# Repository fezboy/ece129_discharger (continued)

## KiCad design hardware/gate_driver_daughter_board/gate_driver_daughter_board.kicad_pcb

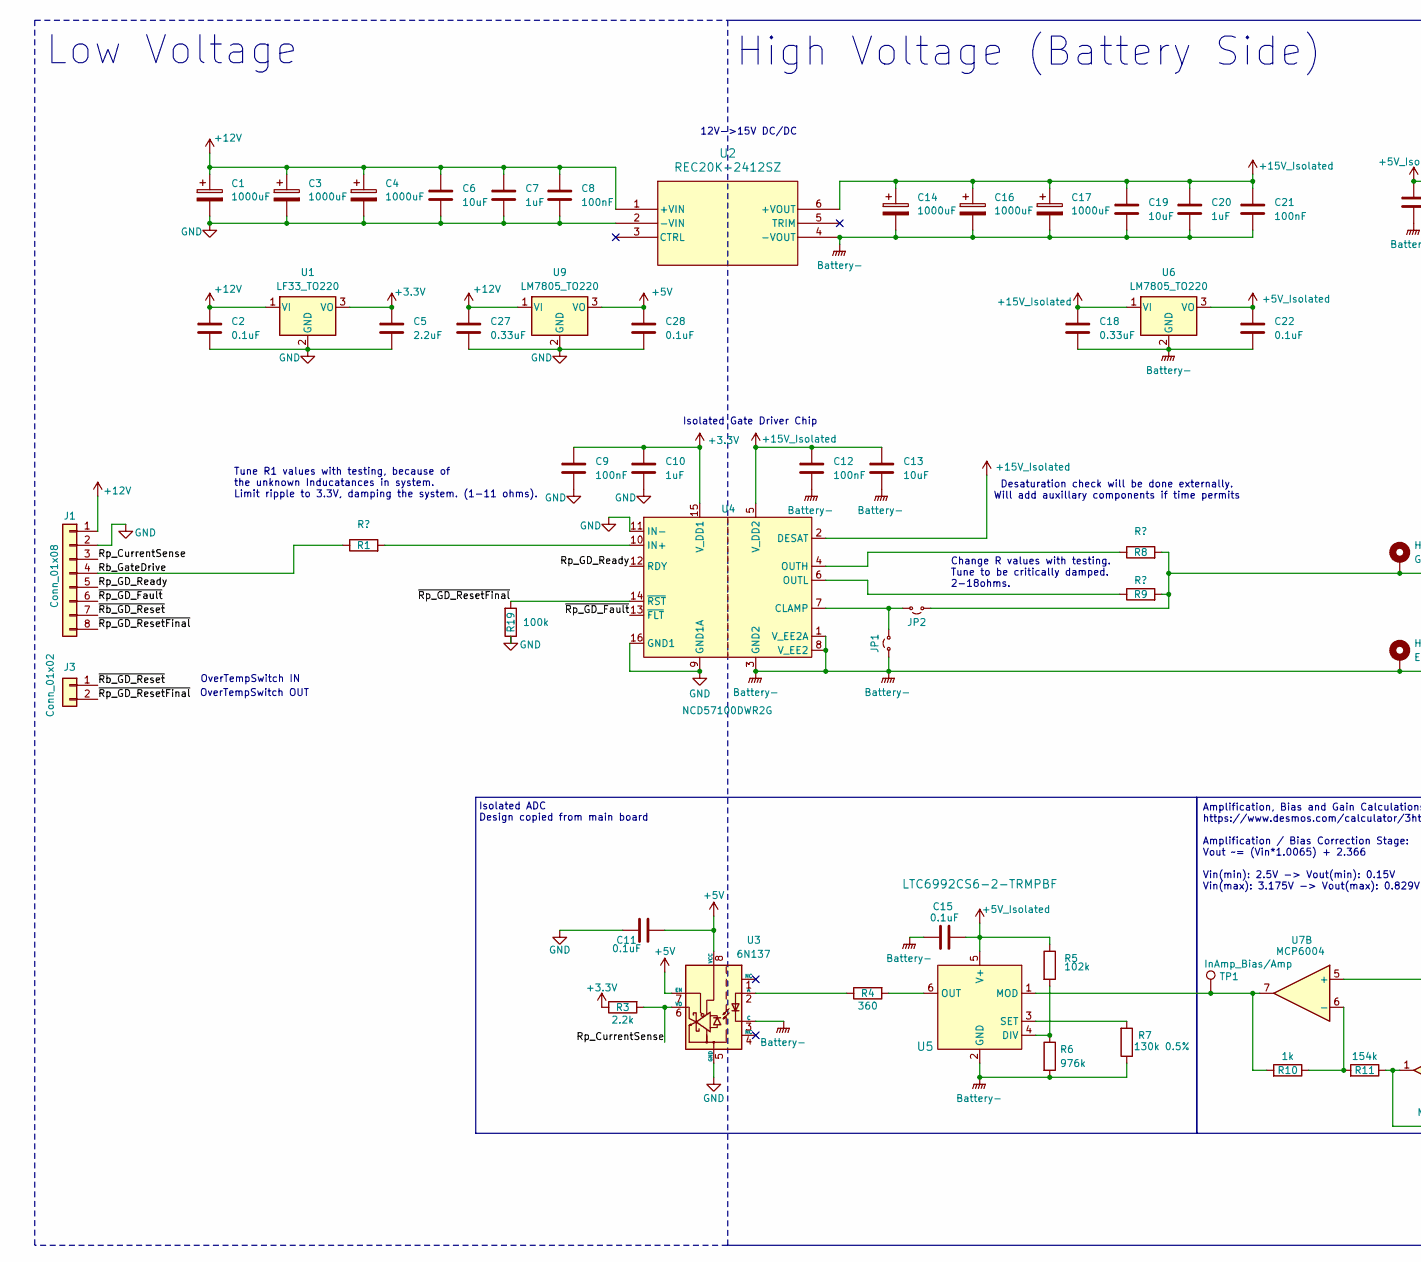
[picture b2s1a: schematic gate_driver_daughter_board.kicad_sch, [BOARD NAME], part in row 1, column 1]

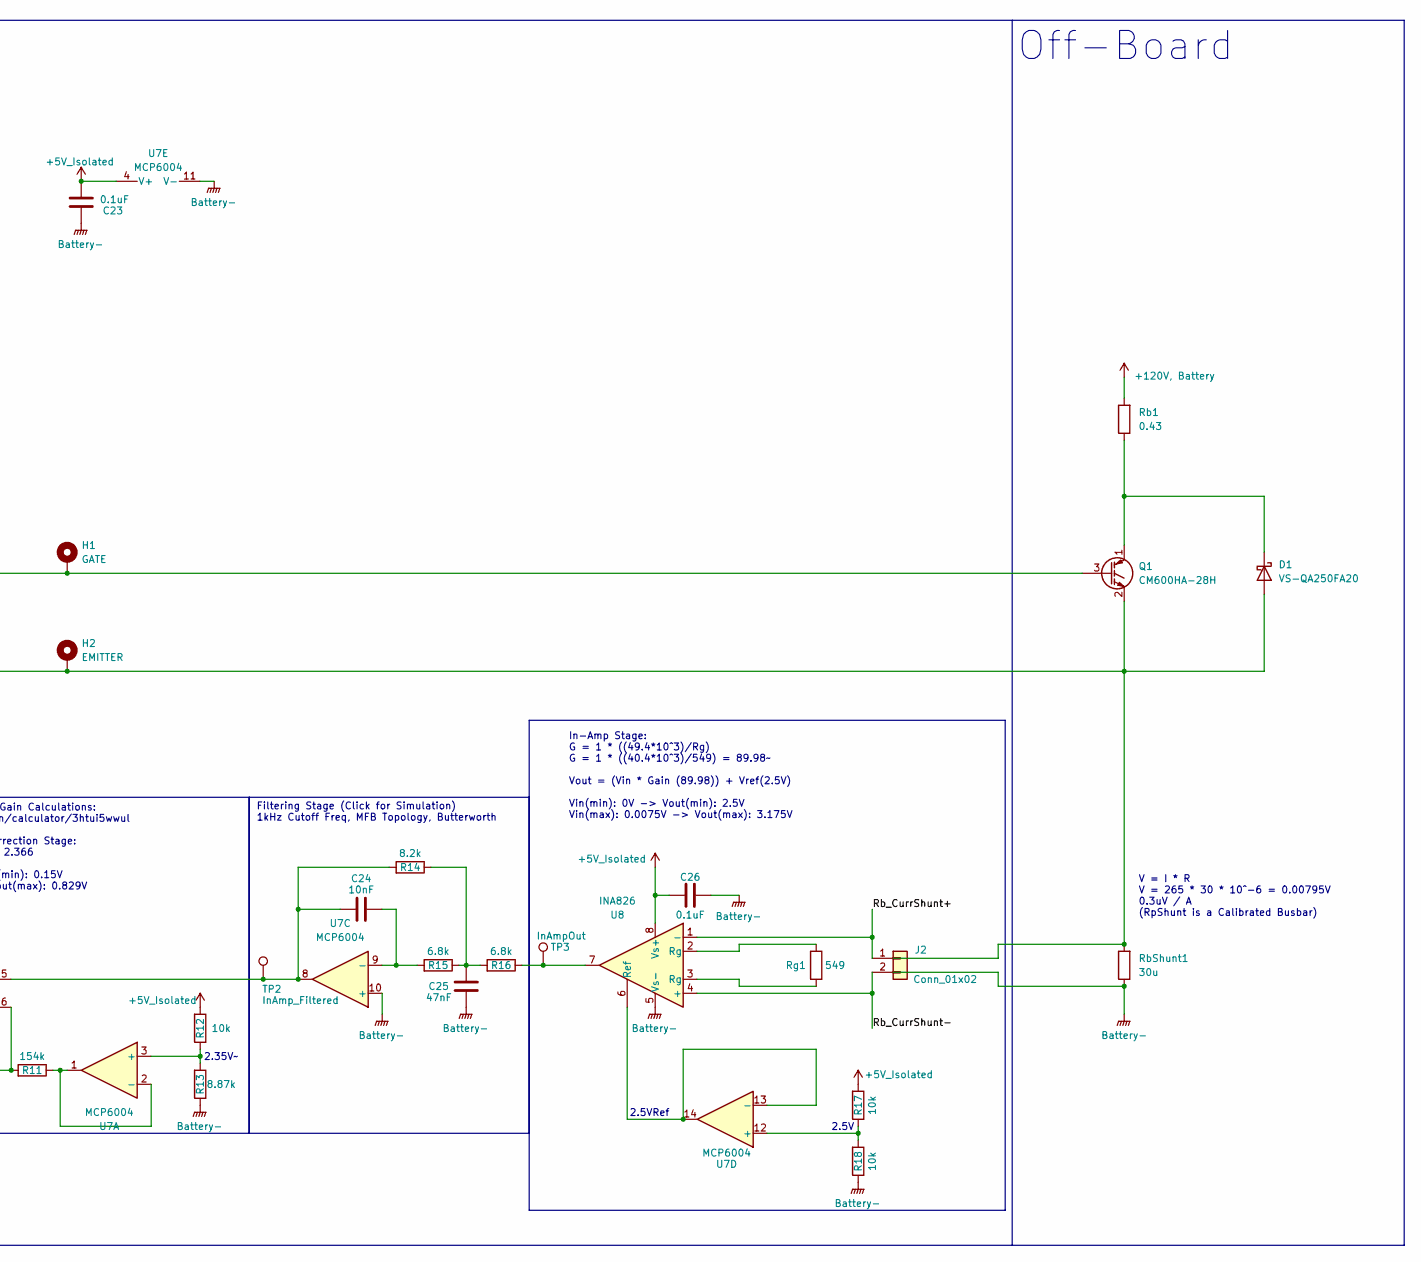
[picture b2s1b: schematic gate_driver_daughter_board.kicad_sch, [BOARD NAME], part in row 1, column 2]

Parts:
C1, C3, C4, C14, C16, C17: 1000uF; 25V1000uF; Manufacturer Part Number Nichicon; Digikey Part Number UVY1E102MPD1TD
C2, C11, C15, C22, C23, C26, C28: 0.1uF; C_0805_2012Metric_Pad1.18x1.45mm_HandSolder
C5: 2.2uF; C_0805_2012Metric_Pad1.18x1.45mm_HandSolder
C6, C13, C19: 10uF; C_0805_2012Metric_Pad1.18x1.45mm_HandSolder
C7, C10, C20: 1uF; C_0805_2012Metric_Pad1.18x1.45mm_HandSolder
C8, C9, C12, C21: 100nF; C_0805_2012Metric_Pad1.18x1.45mm_HandSolder
C18, C27: 0.33uF; C_0805_2012Metric_Pad1.18x1.45mm_HandSolder
C24: 10nF; C_0805_2012Metric_Pad1.18x1.45mm_HandSolder
C25: 47nF; C_0805_2012Metric_Pad1.18x1.45mm_HandSolder
D1: VS-QA250FA20; Manufacturer Part Number Vishay Semiconductors; Digikey Part Number 78-VS-QA250FA20
H1: GATE; MountingHole_4.3x6.2mm_M4_Pad
H2: EMITTER; MountingHole_4.3x6.2mm_M4_Pad
J1: Conn_01x08; Molex_Nano-Fit_105309-xx08_1x08_P2.50mm_Vertical
J2, J3: Conn_01x02; Molex_Nano-Fit_105309-xx02_1x02_P2.50mm_Vertical
JP1, JP2: Jumper_2_Small_Open; PinHeader_1x02_P2.54mm_Vertical
Q1: CM600HA-28H
R1, R8, R9: R?; R_1206_3216Metric_Pad1.30x1.75mm_HandSolder
R3: 2.2k; R_0805_2012Metric_Pad1.20x1.40mm_HandSolder
R4: 360; R_0805_2012Metric_Pad1.20x1.40mm_HandSolder
R5: 102k; R_0805_2012Metric_Pad1.20x1.40mm_HandSolder
R6: 976k; R_0805_2012Metric_Pad1.20x1.40mm_HandSolder
R7: 130k 0.5%; R_0805_2012Metric_Pad1.20x1.40mm_HandSolder
R10: 1k; R_0805_2012Metric_Pad1.20x1.40mm_HandSolder
R11: 154k; R_0805_2012Metric_Pad1.20x1.40mm_HandSolder
R12, R17, R18: 10k; R_0805_2012Metric_Pad1.20x1.40mm_HandSolder
R13: 8.87k; R_0805_2012Metric_Pad1.20x1.40mm_HandSolder
R14: 8.2k; R_0805_2012Metric_Pad1.20x1.40mm_HandSolder
R15, R16: 6.8k; R_0805_2012Metric_Pad1.20x1.40mm_HandSolder
R19: 100k; R_0805_2012Metric_Pad1.20x1.40mm_HandSolder
Rb1: 0.43
RbShunt1: 30u
Rg1: 549; R_0805_2012Metric_Pad1.20x1.40mm_HandSolder
TP1: InAmp_Bias/Amp; TestPoint_Pad_D3.0mm
TP2: InAmp_Filtered; TestPoint_Pad_D3.0mm
TP3: InAmpOut; TestPoint_Pad_2.0x2.0mm
U1: LF33_TO220; TO-220-3_Vertical
U2: REC20K-2412SZ; REC20K_RCP
U3: 6N137; DIP-8_W7.62mm
U4: NCD57100DWR2G; SOIC-16W_7.5x10.3mm_P1.27mm; MFG PN NCD57100DWR2G; Digi PN 488-NCD57100DWR2GTR-ND
U5: LTC6992CS6-2-TRMPBF; TSOT-23-6; MFG PN LTC6992CS6-2-TRMPBF; Digi PN 505-LTC6992CS6-2#TRMPBFCT-ND
U6, U9: LM7805_TO220; TO-220-3_Vertical
U7: MCP6004; SOIC-14_3.9x8.7mm_P1.27mm
U8: INA826; SOIC-8_3.9x4.9mm_P1.27mm

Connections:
+3.3V: C5.2, C9.2, C10.2, R3.1, U1.3 (VO), U4.15 (V_DD1)
+5V: C11.1, C28.2, U3.7 (EN), U3.8 (VCC), U9.3 (VO)
+5V_Isolated: C15.1, C22.2, C23.2, C26.2, R5.1, R12.2, R17.2, U5.5 (V+), U6.3 (VO), U7.4 (V+), U8.8 (Vs+)
+12V: C1.1, C2.2, C3.1, C4.1, C6.2, C7.2, C8.2, C27.2, J1.1, U1.1 (VI), U2.1 (+VIN), U9.1 (VI)
+15V_Isolated: C12.2, C13.2, C14.1, C16.1, C17.1, C18.2, C19.2, C20.2, C21.2, U2.6 (+VOUT), U4.2 (DESAT), U4.5 (V_DD2), U6.1 (VI)
/Rb_CurrShunt+: J2.1, U8.1 (-)
/Rb_CurrShunt-: J2.2, U8.4 (+)
/Rb_GateDrive: J1.4, R1.1
/Rp_CurrentSense: J1.3, R3.2, U3.6 (VO)
/Rp_GD_Ready: J1.5, U4.12 (RDY)
/~Rb_GD_Reset: J1.7, J3.1
/~Rp_GD_Fault: J1.6, U4.13 (~FLT)
/~Rp_GD_ResetFinal: J1.8, J3.2, R19.2, U4.14 (~RST)
Battery-: C12.1, C13.1, C14.2, C15.2, C16.2, C17.2, C18.1, C19.1, C20.1, C21.1, C22.1, C23.1, C25.1, C26.1, D1.2 (A), H2.MP (MP_MP), JP1.1 (A), Q1.2 (E), R6.2, R7.1, R13.1, R18.1, RbShunt1.1, RbShunt1.2, U2.4 (-VOUT), U3.3 (C), U4.1 (V_EE2A), U4.3 (GND2), U4.8 (V_EE2), U5.2 (GND), U6.2 (GND), U7.10 (+), U7.11 (V-), U8.5 (Vs-)
GND: C1.2, C2.1, C3.2, C4.2, C5.1, C6.1, C7.1, C8.1, C9.1, C10.1, C11.2, C27.1, C28.1, J1.2, R19.1, U1.2 (GND), U2.2 (-VIN), U3.5 (GND), U4.9 (GND1A), U4.11 (IN-), U4.16 (GND1), U9.2 (GND)
unnamed: C25.2, R14.1, R15.1, R16.2
unnamed: D1.1 (K), Q1.1 (C), Rb1.1
unnamed: JP1.2 (B), JP2.2 (B), U4.7 (CLAMP)
unnamed: H1.MP (MP_MP), JP2.1 (A), Q1.3 (G), R8.2, R9.2
unnamed: R16.1, TP3.1 (1_1), U8.7
unnamed: Rg1.1, U8.2 (Rg)
unnamed: Rg1.2, U8.3 (Rg)
unnamed: R4.1, U3.2 (A)
unnamed: R1.2, U4.10 (IN+)
unnamed: R8.1, U4.4 (OUTH)
unnamed: R9.1, U4.6 (OUTL)
unnamed: R5.2, R6.1, U5.4 (DIV)
unnamed: R10.2, TP1.1 (1_1), U5.1 (MOD), U7.7
unnamed: R4.2, U5.6 (OUT)
unnamed: R7.2, U5.3 (SET)
unnamed: R12.1, R13.2, U7.3 (+)
unnamed: R11.1, U7.1, U7.2 (-)
unnamed: C24.1, R14.2, TP2.1 (1_1), U7.5 (+), U7.8
unnamed: R10.1, R11.2, U7.6 (-)
unnamed: C24.2, R15.2, U7.9 (-)
unnamed: R17.1, R18.2, U7.12 (+)
unnamed: U7.13 (-), U7.14, U8.6 (Ref)

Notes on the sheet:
Isolated Gate Driver Chip
Amplification, Bias and Gain Calculations: https://www.desmos.com/calculator/3htui5wwul Amplification / Bias Correction Stage: Vout ~= (Vin*1.0065) + 2.366 Vin(min): 2.5V -> Vout(min): 0.15V Vin(max): 3.175V -> Vout(max): 0.829V
2.35V~
12V->15V DC/DC
In-Amp Stage: G = 1 * ((49.4*10^3)/Rg) G = 1 * ((40.4*10^3)/549) = 89.98~ Vout = (Vin * Gain (89.98)) + Vref(2.5V) Vin(min): 0V -> Vout(min): 2.5V Vin(max): 0.0075V -> Vout(max): 3.175V
Low Voltage
Desaturation check will be done externally. Will add auxillary components if time permits
Isolated ADC Design copied from main board
2.5VRef
OverTempSwitch OUT
2.5V
V = I * R V = 265 * 30 * 10^-6 = 0.00795V 0.3uV / A (RpShunt is a Calibrated Busbar)
Tune R1 values with testing, because of the unknown Inducatances in system. Limit ripple to 3.3V, damping the system. (1-11 ohms).
OverTempSwitch IN
Off-Board
High Voltage (Battery Side)
Change R values with testing. Tune to be critically damped. 2-18ohms.
Filtering Stage (Click for Simulation) 1kHz Cutoff Freq, MFB Topology, Butterworth

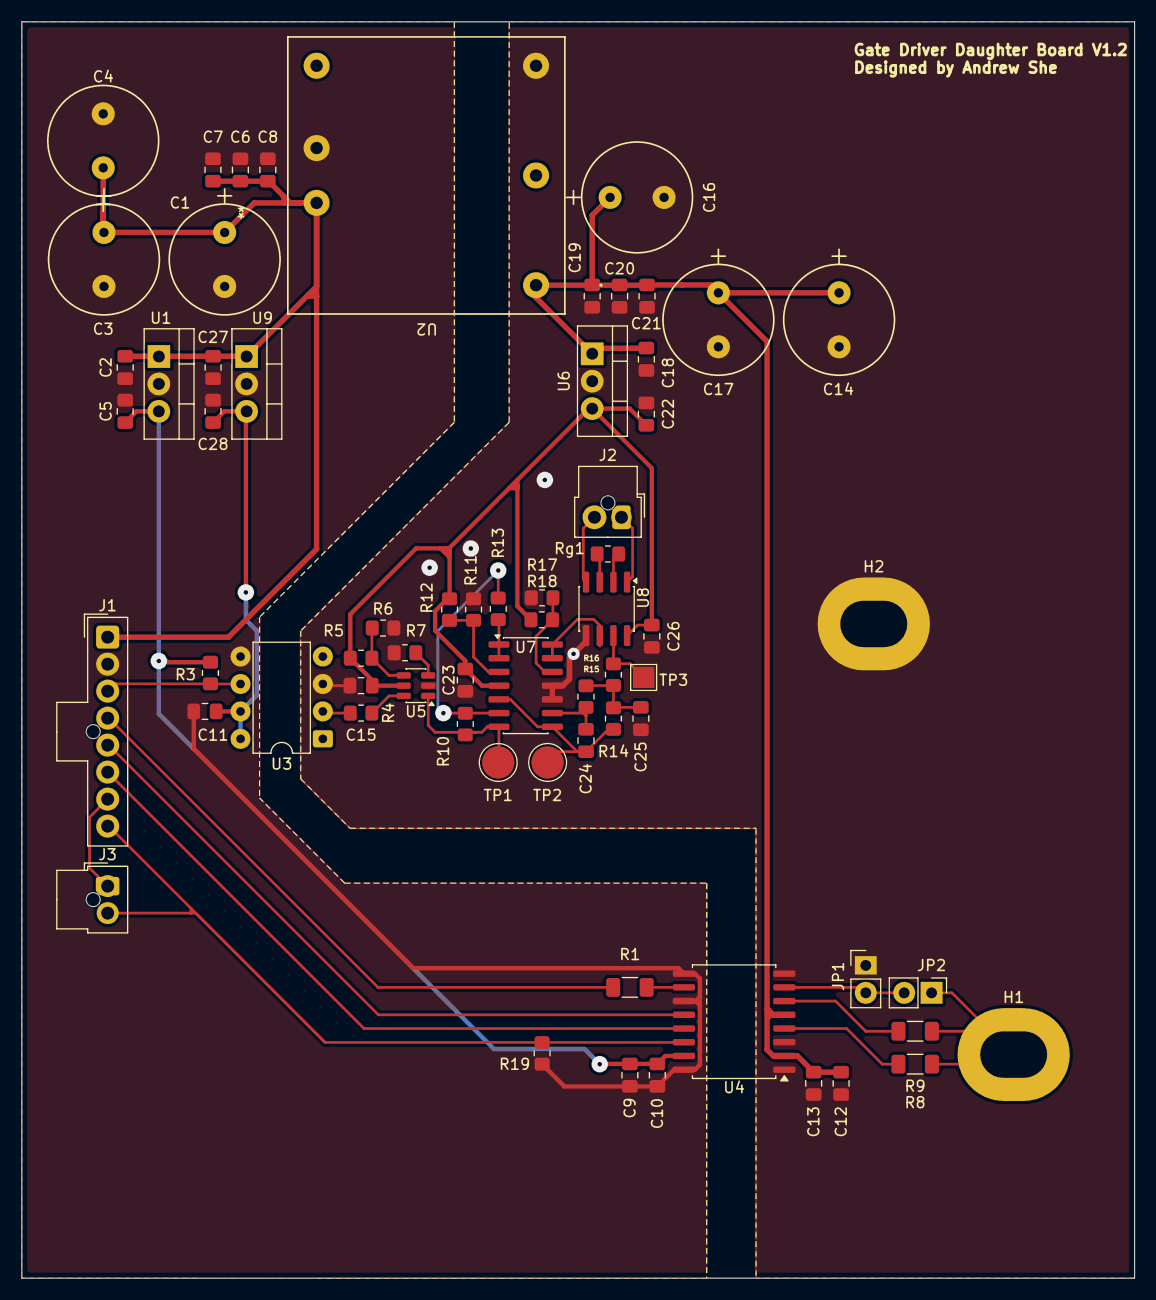
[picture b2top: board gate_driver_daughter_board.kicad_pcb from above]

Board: 2 copper layers, 103.0 x 116.3 mm, 66 parts (0 on the bottom side), 36 nets.

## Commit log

2026-04-06 Add symbol librarie and NUCLEO-L432KC
2026-04-08 Add Gate Driver Daughter Board subproject
2026-04-08 Add main board subpages
2026-04-23 Rust blinky and screen hello-world
2026-04-23 Copied code from USB example
    Doesn't work, crashes during config
2026-04-23 Added NCD57100DWR2G Gate Driver Symbol (Daughter Board Library)
2026-04-23 MBR0.0.1 - Begin addition of sheet pins to MCU page
    Incomplete
2026-04-27 temperature sensing initial
2026-04-28 Got USB Serial working!
2026-04-28 sensing schematics
2026-05-01 R0.0.2 Add more connections to MCU, some connectors
    commit d1f92fde9a9b01f608e388bb27e003f4547c4ba5
    Author: fezboy <31973884+fezboy@users.noreply.github.com>
    Date: Tue Apr 28 12:29:51 2026 -0700
    R0.0.2 Add more connections to MCU, some connectors
2026-05-01 pushing all changes
2026-05-01 Add LTC6992CS6-2#TRMPBF to project symbol library
2026-05-01 bad attempt at initialization abstraction
2026-05-01 Abstract out board struct, add QEI
2026-05-02 Add NUCLEO-H503RB Symbol
2026-05-02 R0.0.3 Correct Voltage measurement frequency and divider
2026-05-04 DC/DC added, incomplete Current sense, and incomplete snubber circuit
2026-05-04 basic pwm for gate driver
2026-05-06 Pre-Testing Changes (Used for Presentation Graphics)
2026-05-08 Add 74LVC1T45W6-7 Symbol
2026-05-08 Start work on MCU Connections
2026-05-08 new sensor changes, need to still add low pass for voltage
2026-05-10 adding connectors
2026-05-12 DC/DC Change
2026-05-12 chebyshev filter for voltage sense 2.0
2026-05-13 Pin assignment first draft
2026-05-13 Filter Stage Added, Current Gain Stage Added, Simulation Added
2026-05-13 Final Schematic Changes, Footprints assigned, ready for review / layout
2026-05-13 changes to sensing and footprints added
2026-05-14 PCBrev1
2026-05-14 Add Isolation Keepout Zone, little bit of ground routing
2026-05-14 Annular Ring Adjustment
2026-05-15 V1.0 PCB Ready to Mill, Gate Driver Daughter Board
2026-05-15 V1.1, M60 Milling Accomodations
2026-05-15 V1.2, JLC Order PCB Updates
2026-05-18 completed main board schematic
2026-05-20 changes to battery connector
2026-05-22 initial layout, power traces remain
2026-05-23 Finished Layout and routing
    * Flipped CAN transceiver upside down on schematic
    * Moved CAN transceiver nearer to J13 and MCU CAN pins
    * Moved 5V DCDC caps nearer to 5V DCDC
    * Moved Silkscreen out from under U9
    * Moved J2 and J1 to prevent plugging 12V into a temp sensor connector
    * Change +3.3V to +3V3 to match MCU page
2026-05-23 Fix up silkscreen, testpoints, and one more decoupler
2026-05-23 final rev 1.0 complete
